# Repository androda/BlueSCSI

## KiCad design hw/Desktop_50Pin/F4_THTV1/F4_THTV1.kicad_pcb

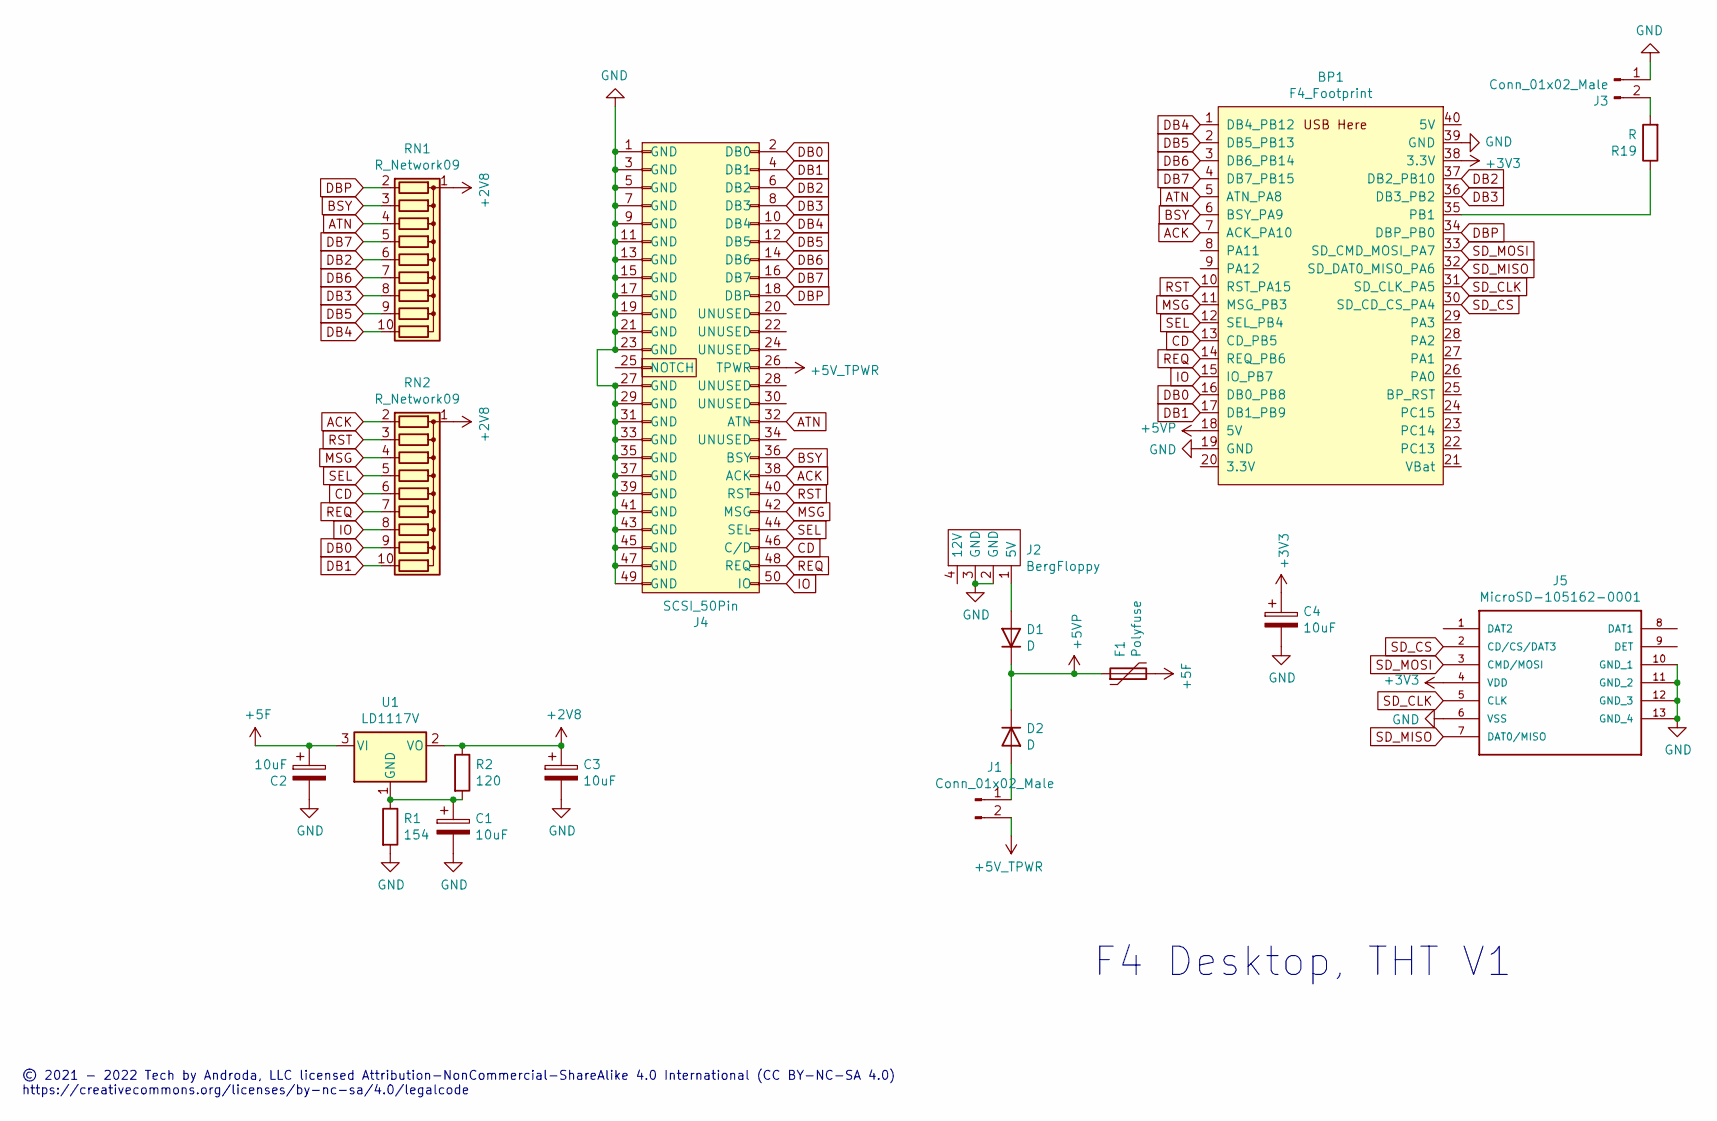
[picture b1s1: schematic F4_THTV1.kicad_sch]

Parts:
BP1: F4_Footprint; BluePillModule
C1, C2, C3, C4: 10uF; C_1210_3225Metric_Pad1.42x2.65mm_HandSolder
D1, D2: D; D_A-405_P7.62mm_Horizontal
F1: Polyfuse; Fuse_BelFuse_0ZRE0005FF_L8.3mm_W3.8mm
J1, J3: Conn_01x02_Male; PinHeader_1x02_P2.54mm_Vertical
J2: BergFloppy; BergFloppy_RightAngle
J4: SCSI_50Pin; SCSI_Internal_50Pin
J5: MicroSD-105162-0001; microsd_molex_1051620001; MANUFACTURER_PART_NUMBER 105162-0001; MOUSER_PART_NUMBER 538-105162-0001
R1: 154; R_Axial_DIN0207_L6.3mm_D2.5mm_P10.16mm_Horizontal
R2: 120; R_Axial_DIN0204_L3.6mm_D1.6mm_P5.08mm_Vertical
R19: R; R_Axial_DIN0207_L6.3mm_D2.5mm_P7.62mm_Horizontal
RN1, RN2: R_Network09; R_Array_SIP10
U1: LD1117V; TO-220-3_Horizontal_TabDown

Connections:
+2V8: C3.1, R2.1, RN1.1 (common), RN2.1 (common), U1.2 (VO)
+3V3: BP1.38 (3.3V), C4.1, J5.4 (VDD)
+5F: C2.1, F1.2, U1.3 (VI)
+5V: J1.2, J4.26 (TPWR)
+5VP: BP1.18 (5V), D1.1 (K), D2.1 (K), F1.1
ACK: BP1.7 (ACK_PA10), J4.38 (ACK), RN2.2 (R1)
ATN: BP1.5 (ATN_PA8), J4.32 (ATN), RN1.4 (R3)
BSY: BP1.6 (BSY_PA9), J4.36 (BSY), RN1.3 (R2)
CD: BP1.13 (CD_PB5), J4.46 (C/D), RN2.6 (R5)
DB0: BP1.16 (DB0_PB8), J4.2 (DB0), RN2.9 (R8)
DB1: BP1.17 (DB1_PB9), J4.4 (DB1), RN2.10 (R9)
DB2: BP1.37 (DB2_PB10), J4.6 (DB2), RN1.6 (R5)
DB3: BP1.36 (DB3_PB2), J4.8 (DB3), RN1.8 (R7)
DB4: BP1.1 (DB4_PB12), J4.10 (DB4), RN1.10 (R9)
DB5: BP1.2 (DB5_PB13), J4.12 (DB5), RN1.9 (R8)
DB6: BP1.3 (DB6_PB14), J4.14 (DB6), RN1.7 (R6)
DB7: BP1.4 (DB7_PB15), J4.16 (DB7), RN1.5 (R4)
DBP: BP1.34 (DBP_PB0), J4.18 (DBP), RN1.2 (R1)
GND: BP1.19 (GND), BP1.39 (GND), C1.2, C2.2, C3.2, C4.2, J2.2 (GND), J2.3 (GND), J3.1, J4.1 (GND), J4.3 (GND), J4.5 (GND), J4.7 (GND), J4.9 (GND), J4.11 (GND), J4.13 (GND), J4.15 (GND), J4.17 (GND), J4.19 (GND), J4.21 (GND), J4.23 (GND), J4.27 (GND), J4.29 (GND), J4.31 (GND), J4.33 (GND), J4.35 (GND), J4.37 (GND), J4.39 (GND), J4.41 (GND), J4.43 (GND), J4.45 (GND), J4.47 (GND), J4.49 (GND), J5.6 (VSS), J5.10 (GND_1), J5.11 (GND_2), J5.12 (GND_3), J5.13 (GND_4), R1.2
IO: BP1.15 (IO_PB7), J4.50 (IO), RN2.8 (R7)
MSG: BP1.11 (MSG_PB3), J4.42 (MSG), RN2.4 (R3)
unnamed: BP1.35 (PB1), R19.1
unnamed: C1.1, R1.1, R2.2, U1.1 (GND)
unnamed: D1.2 (A), J2.1 (5V)
unnamed: D2.2 (A), J1.1
unnamed: J3.2, R19.2
REQ: BP1.14 (REQ_PB6), J4.48 (REQ), RN2.7 (R6)
RST: BP1.10 (RST_PA15), J4.40 (RST), RN2.3 (R2)
SD_CLK: BP1.31 (SD_CLK_PA5), J5.5 (CLK)
SD_CS: BP1.30 (SD_CD_CS_PA4), J5.2 (CD/CS/DAT3)
SD_MISO: BP1.32 (SD_DAT0_MISO_PA6), J5.7 (DAT0/MISO)
SD_MOSI: BP1.33 (SD_CMD_MOSI_PA7), J5.3 (CMD/MOSI)
SEL: BP1.12 (SEL_PB4), J4.44 (SEL), RN2.5 (R4)

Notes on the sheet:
F4 Desktop, THT V1
© 2021 - 2022 Tech by Androda, LLC licensed Attribution-NonCommercial-ShareAlike 4.0 International (CC BY-NC-SA 4.0) https://creativecommons.org/licenses/by-nc-sa/4.0/legalcode

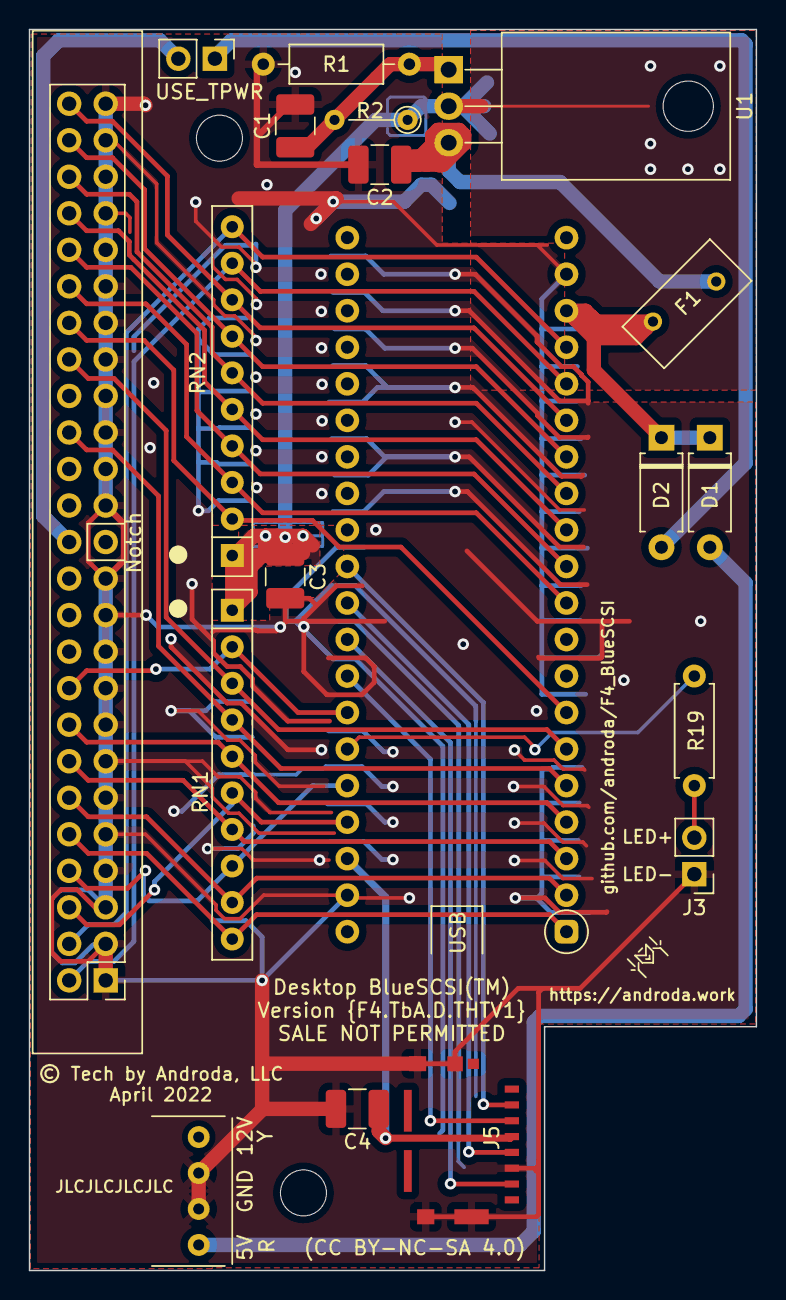
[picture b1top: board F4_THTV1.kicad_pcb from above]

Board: 2 copper layers, 50.5 x 86.3 mm, 19 parts (0 on the bottom side), 33 nets.

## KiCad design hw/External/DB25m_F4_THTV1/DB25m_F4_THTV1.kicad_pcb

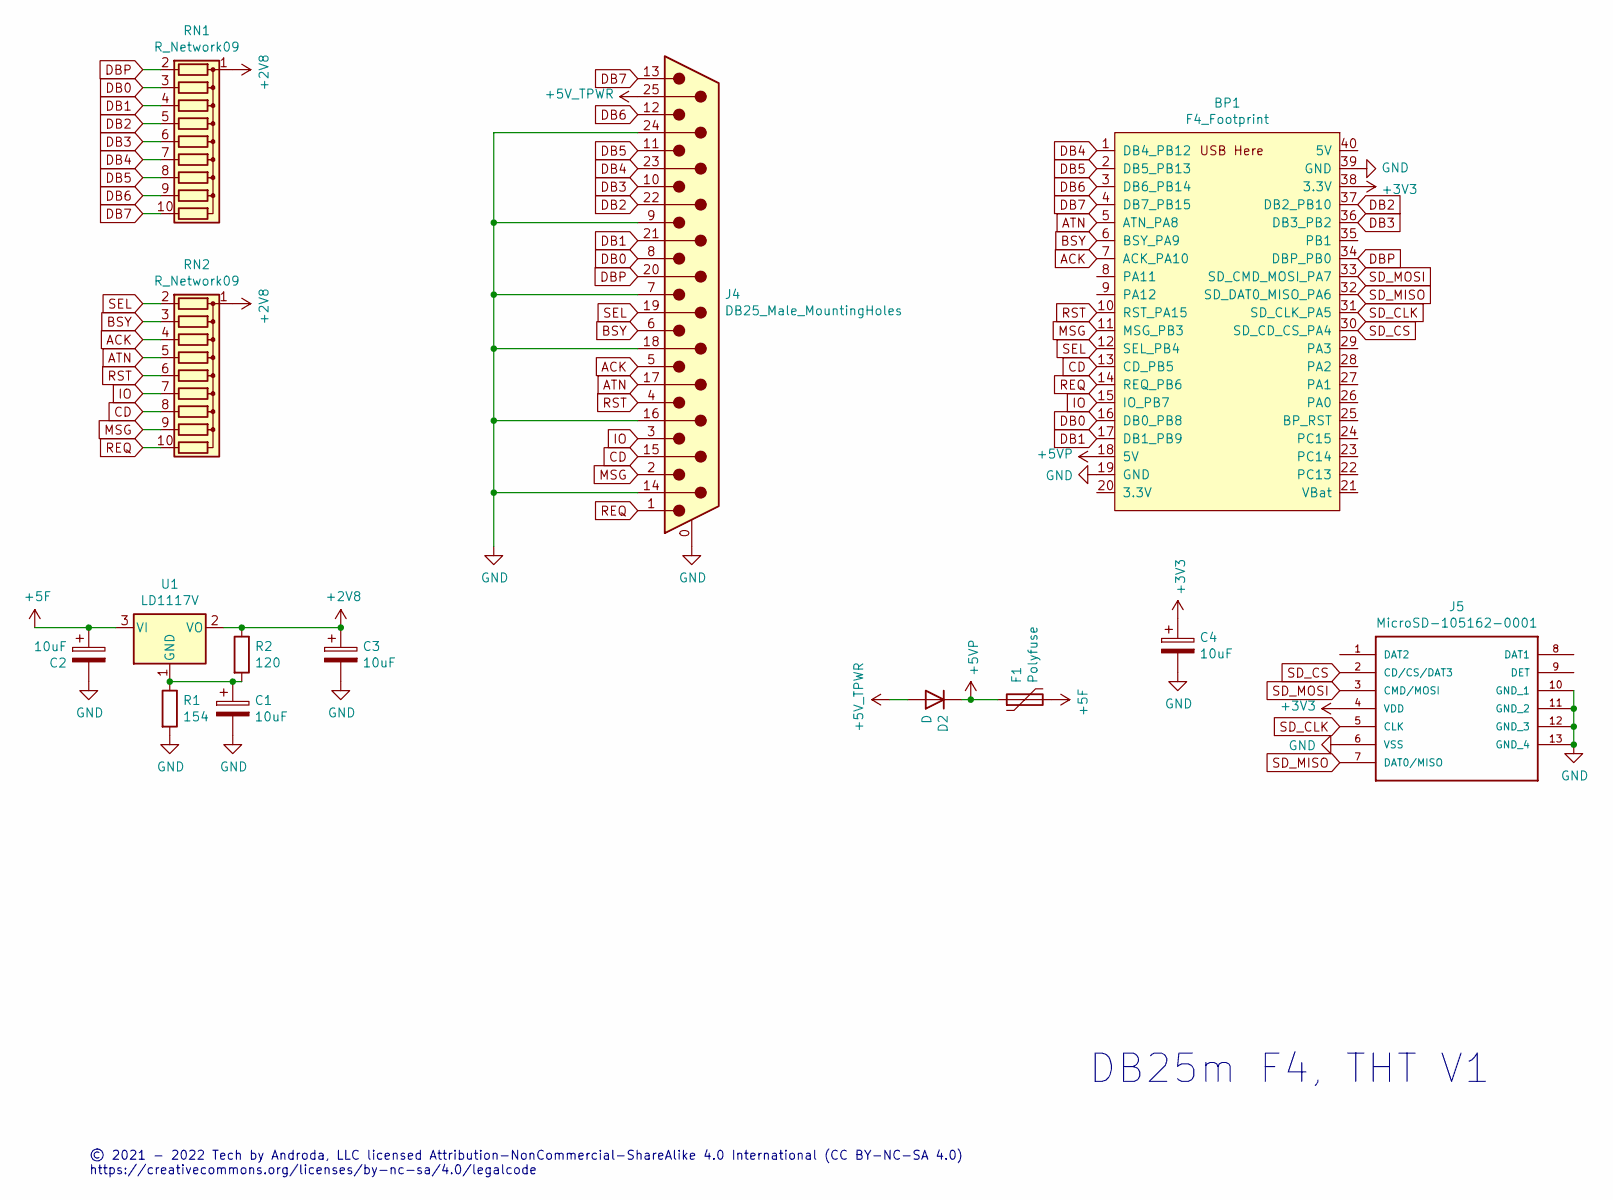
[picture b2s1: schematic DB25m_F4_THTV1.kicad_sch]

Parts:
BP1: F4_Footprint; BluePillModule
C1, C2, C3, C4: 10uF; C_1210_3225Metric_Pad1.42x2.65mm_HandSolder
D2: D; D_A-405_P10.16mm_Horizontal
F1: Polyfuse; Fuse_BelFuse_0ZRE0005FF_L8.3mm_W3.8mm
J4: DB25_Male_MountingHoles; DSUB-25_Male_Horizontal_P2.77x2.84mm_EdgePinOffset7.70mm_Ho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
J5: MicroSD-105162-0001; microsd_molex_1051620001; MANUFACTURER_PART_NUMBER 105162-0001; MOUSER_PART_NUMBER 538-105162-0001
R1: 154; R_Axial_DIN0207_L6.3mm_D2.5mm_P10.16mm_Horizontal
R2: 120; R_Axial_DIN0204_L3.6mm_D1.6mm_P5.08mm_Vertical
RN1, RN2: R_Network09; R_Array_SIP10
U1: LD1117V; TO-220-3_Horizontal_TabDown

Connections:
+2V8: C3.1, R2.1, RN1.1 (common), RN2.1 (common), U1.2 (VO)
+3V3: BP1.38 (3.3V), C4.1, J5.4 (VDD)
+5F: C2.1, F1.2, U1.3 (VI)
+5V: D2.2 (A), J4.25
+5VP: BP1.18 (5V), D2.1 (K), F1.1
ACK: BP1.7 (ACK_PA10), J4.5, RN2.4 (R3)
ATN: BP1.5 (ATN_PA8), J4.17, RN2.5 (R4)
BSY: BP1.6 (BSY_PA9), J4.6, RN2.3 (R2)
CD: BP1.13 (CD_PB5), J4.15, RN2.8 (R7)
DB0: BP1.16 (DB0_PB8), J4.8, RN1.3 (R2)
DB1: BP1.17 (DB1_PB9), J4.21, RN1.4 (R3)
DB2: BP1.37 (DB2_PB10), J4.22, RN1.5 (R4)
DB3: BP1.36 (DB3_PB2), J4.10, RN1.6 (R5)
DB4: BP1.1 (DB4_PB12), J4.23, RN1.7 (R6)
DB5: BP1.2 (DB5_PB13), J4.11, RN1.8 (R7)
DB6: BP1.3 (DB6_PB14), J4.12, RN1.9 (R8)
DB7: BP1.4 (DB7_PB15), J4.13, RN1.10 (R9)
DBP: BP1.34 (DBP_PB0), J4.20, RN1.2 (R1)
GND: BP1.19 (GND), BP1.39 (GND), C1.2, C2.2, C3.2, C4.2, J4.0 (PAD), J4.7, J4.9, J4.14, J4.16, J4.18, J4.24, J5.6 (VSS), J5.10 (GND_1), J5.11 (GND_2), J5.12 (GND_3), J5.13 (GND_4), R1.2
IO: BP1.15 (IO_PB7), J4.3, RN2.7 (R6)
MSG: BP1.11 (MSG_PB3), J4.2, RN2.9 (R8)
unnamed: C1.1, R1.1, R2.2, U1.1 (GND)
REQ: BP1.14 (REQ_PB6), J4.1, RN2.10 (R9)
RST: BP1.10 (RST_PA15), J4.4, RN2.6 (R5)
SD_CLK: BP1.31 (SD_CLK_PA5), J5.5 (CLK)
SD_CS: BP1.30 (SD_CD_CS_PA4), J5.2 (CD/CS/DAT3)
SD_MISO: BP1.32 (SD_DAT0_MISO_PA6), J5.7 (DAT0/MISO)
SD_MOSI: BP1.33 (SD_CMD_MOSI_PA7), J5.3 (CMD/MOSI)
SEL: BP1.12 (SEL_PB4), J4.19, RN2.2 (R1)

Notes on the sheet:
© 2021 - 2022 Tech by Androda, LLC licensed Attribution-NonCommercial-ShareAlike 4.0 International (CC BY-NC-SA 4.0) https://creativecommons.org/licenses/by-nc-sa/4.0/legalcode
DB25m F4, THT V1

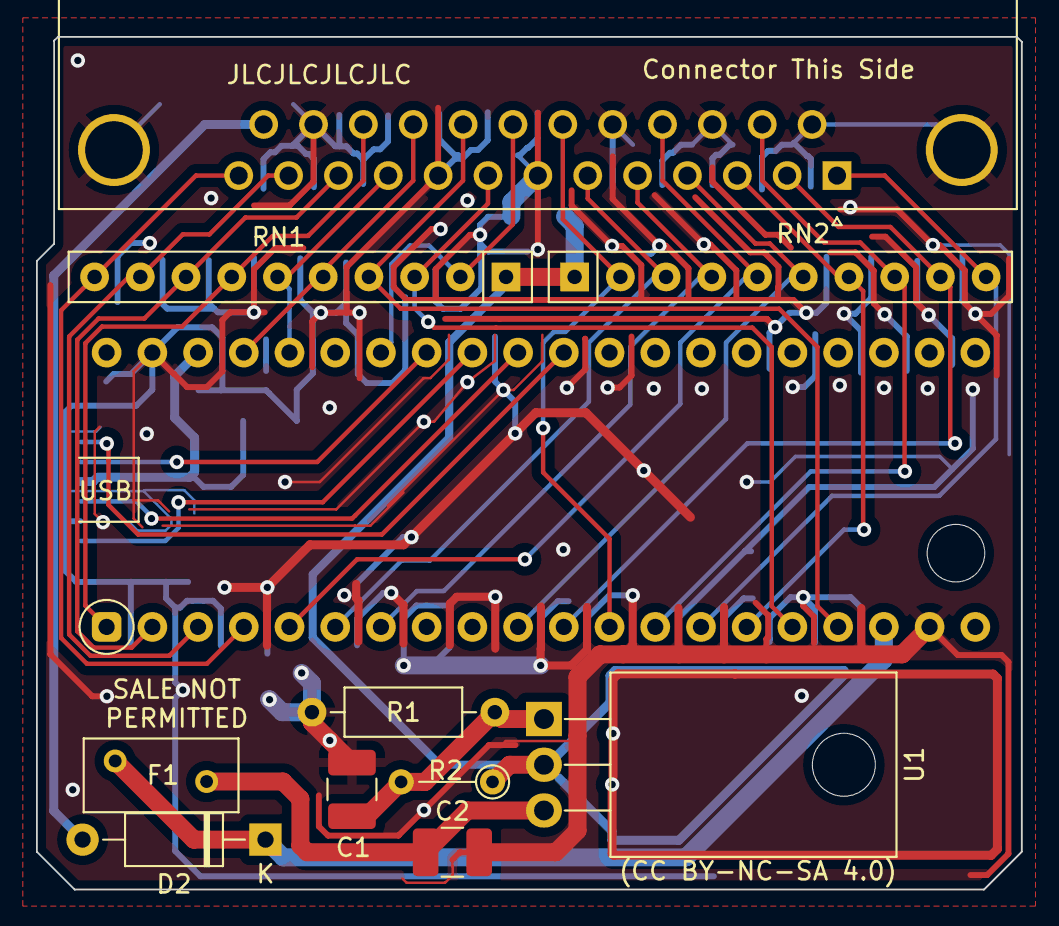
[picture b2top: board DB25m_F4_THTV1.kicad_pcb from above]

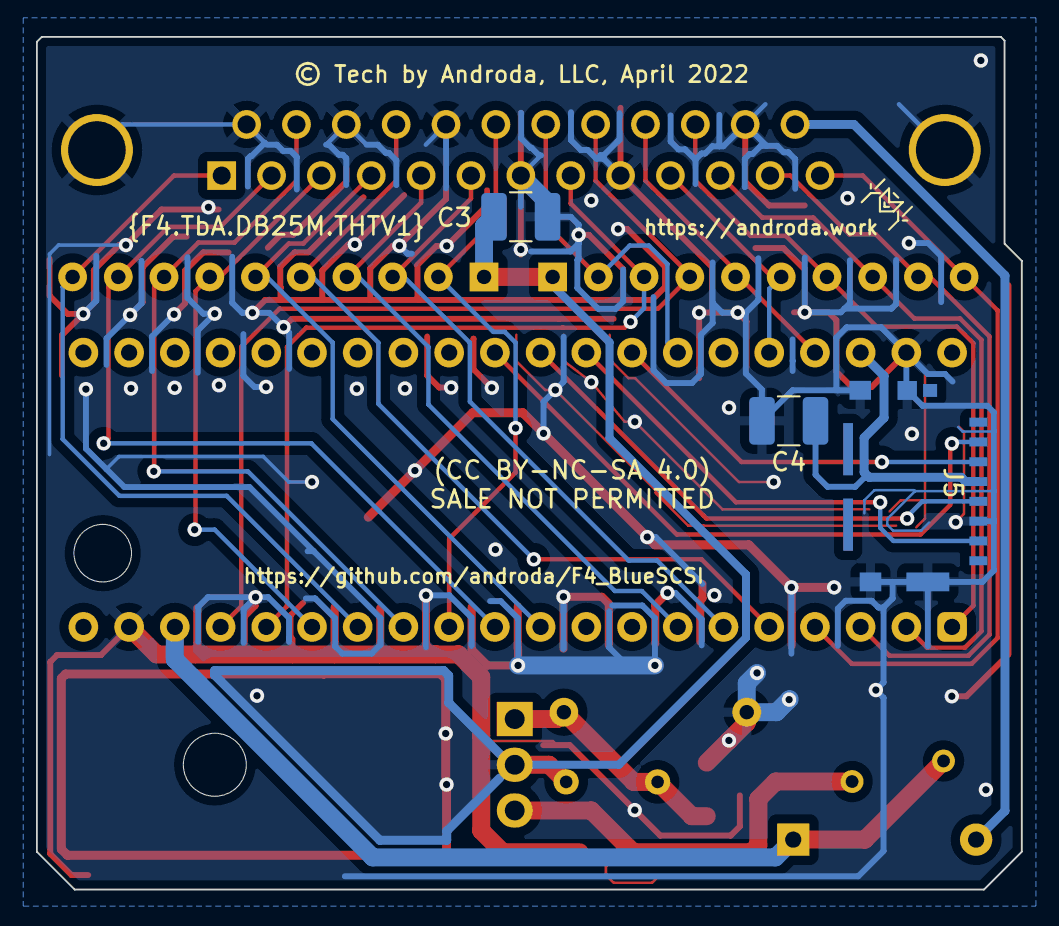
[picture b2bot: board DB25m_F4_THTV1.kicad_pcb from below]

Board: 2 copper layers, 54.7 x 47.4 mm, 14 parts (3 on the bottom side), 29 nets.

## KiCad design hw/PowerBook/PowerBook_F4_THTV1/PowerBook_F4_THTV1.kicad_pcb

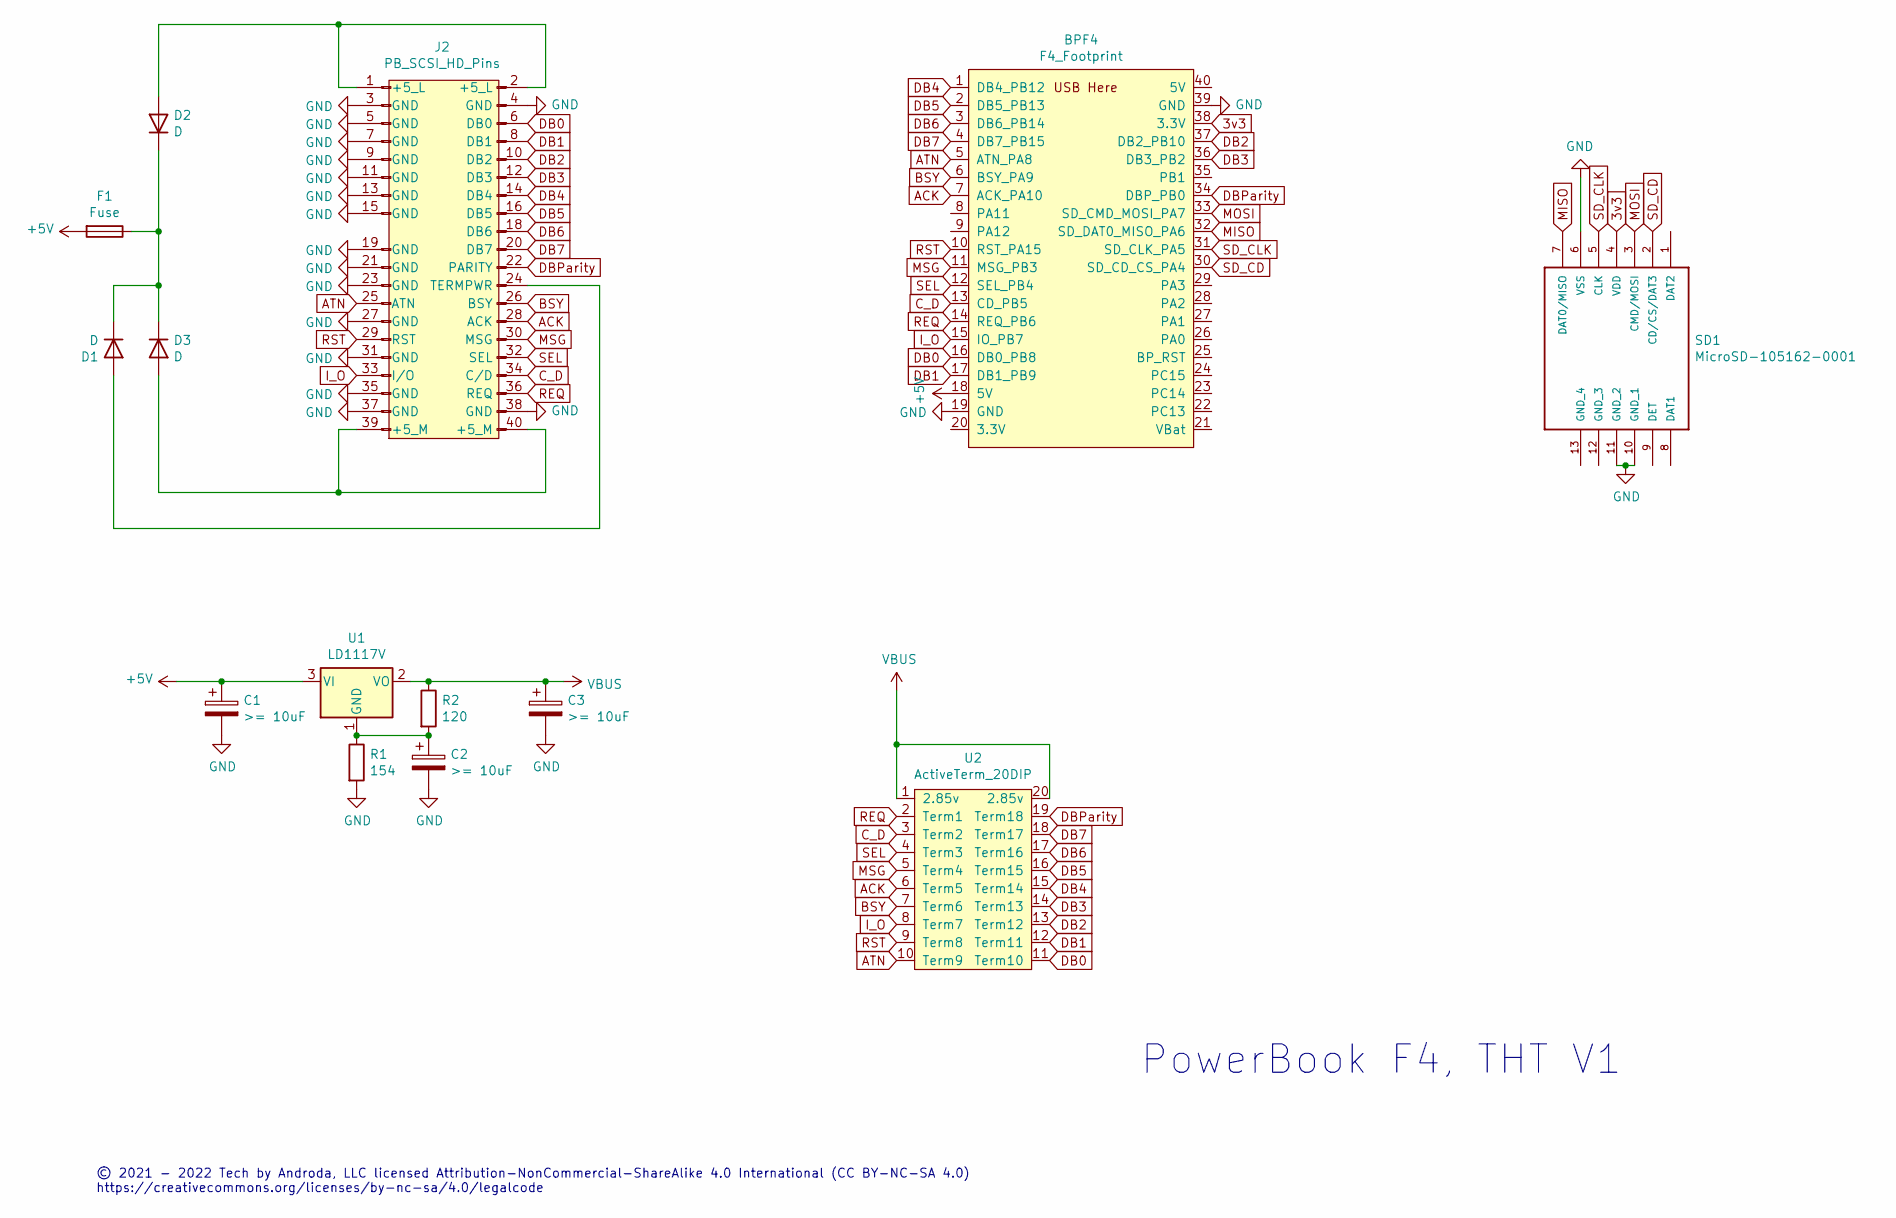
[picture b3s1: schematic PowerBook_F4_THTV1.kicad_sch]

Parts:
BPF4: F4_Footprint; BluePillModule
C1, C2, C3: >= 10uF; C_1206_3216Metric_Pad1.42x1.75mm_HandSolder
D1, D2, D3: D; D_A-405_P10.16mm_Horizontal
F1: Fuse; Fuse_BelFuse_0ZRE0005FF_L8.3mm_W3.8mm
J2: PB_SCSI_HD_Pins; PowerBook_SCSI_40Pin_UpsideDown
R1: 154; R_Axial_DIN0204_L3.6mm_D1.6mm_P7.62mm_Horizontal
R2: 120; R_Axial_DIN0204_L3.6mm_D1.6mm_P5.08mm_Vertical
SD1: MicroSD-105162-0001; microsd_molex_1051620001; MANUFACTURER_PART_NUMBER 105162-0001; MOUSER_PART_NUMBER 538-105162-0001
U1: LD1117V; TO-220-3_Horizontal_TabDown
U2: ActiveTerm_20DIP; DIP-20_W7.62mm_Socket

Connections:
3v3: BPF4.38 (3.3V), SD1.4 (VDD)
+5V: BPF4.18 (5V), C1.1, F1.2, U1.3 (VI)
ACK: BPF4.7 (ACK_PA10), J2.28 (ACK), U2.6 (Term5)
ATN: BPF4.5 (ATN_PA8), J2.25 (ATN), U2.10 (Term9)
BSY: BPF4.6 (BSY_PA9), J2.26 (BSY), U2.7 (Term6)
C_D: BPF4.13 (CD_PB5), J2.34 (C/D), U2.3 (Term2)
DB0: BPF4.16 (DB0_PB8), J2.6 (DB0), U2.11 (Term10)
DB1: BPF4.17 (DB1_PB9), J2.8 (DB1), U2.12 (Term11)
DB2: BPF4.37 (DB2_PB10), J2.10 (DB2), U2.13 (Term12)
DB3: BPF4.36 (DB3_PB2), J2.12 (DB3), U2.14 (Term13)
DB4: BPF4.1 (DB4_PB12), J2.14 (DB4), U2.15 (Term14)
DB5: BPF4.2 (DB5_PB13), J2.16 (DB5), U2.16 (Term15)
DB6: BPF4.3 (DB6_PB14), J2.18 (DB6), U2.17 (Term16)
DB7: BPF4.4 (DB7_PB15), J2.20 (DB7), U2.18 (Term17)
DBParity: BPF4.34 (DBP_PB0), J2.22 (PARITY), U2.19 (Term18)
GND: BPF4.19 (GND), BPF4.39 (GND), C1.2, C2.2, C3.2, J2.3 (GND), J2.4 (GND), J2.5 (GND), J2.7 (GND), J2.9 (GND), J2.11 (GND), J2.13 (GND), J2.15 (GND), J2.19 (GND), J2.21 (GND), J2.23 (GND), J2.27 (GND), J2.31 (GND), J2.35 (GND), J2.37 (GND), J2.38 (GND), R1.2, SD1.6 (VSS), SD1.10 (GND_1), SD1.11 (GND_2)
I_O: BPF4.15 (IO_PB7), J2.33 (I/O), U2.8 (Term7)
MISO: BPF4.32 (SD_DAT0_MISO_PA6), SD1.7 (DAT0/MISO)
MOSI: BPF4.33 (SD_CMD_MOSI_PA7), SD1.3 (CMD/MOSI)
MSG: BPF4.11 (MSG_PB3), J2.30 (MSG), U2.5 (Term4)
unnamed: C2.1, R1.1, R2.2, U1.1 (GND)
unnamed: D1.1 (K), D2.1 (K), D3.1 (K), F1.1
unnamed: D1.2 (A), J2.24 (TERMPWR)
unnamed: D2.2 (A), J2.1 (+5_L), J2.2 (+5_L)
unnamed: D3.2 (A), J2.39 (+5_M), J2.40 (+5_M)
REQ: BPF4.14 (REQ_PB6), J2.36 (REQ), U2.2 (Term1)
RST: BPF4.10 (RST_PA15), J2.29 (RST), U2.9 (Term8)
SD_CD: BPF4.30 (SD_CD_CS_PA4), SD1.2 (CD/CS/DAT3)
SD_CLK: BPF4.31 (SD_CLK_PA5), SD1.5 (CLK)
SEL: BPF4.12 (SEL_PB4), J2.32 (SEL), U2.4 (Term3)
VBUS: C3.1, R2.1, U1.2 (VO), U2.1 (2.85v), U2.20 (2.85v)

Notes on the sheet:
PowerBook F4, THT V1
© 2021 - 2022 Tech by Androda, LLC licensed Attribution-NonCommercial-ShareAlike 4.0 International (CC BY-NC-SA 4.0) https://creativecommons.org/licenses/by-nc-sa/4.0/legalcode

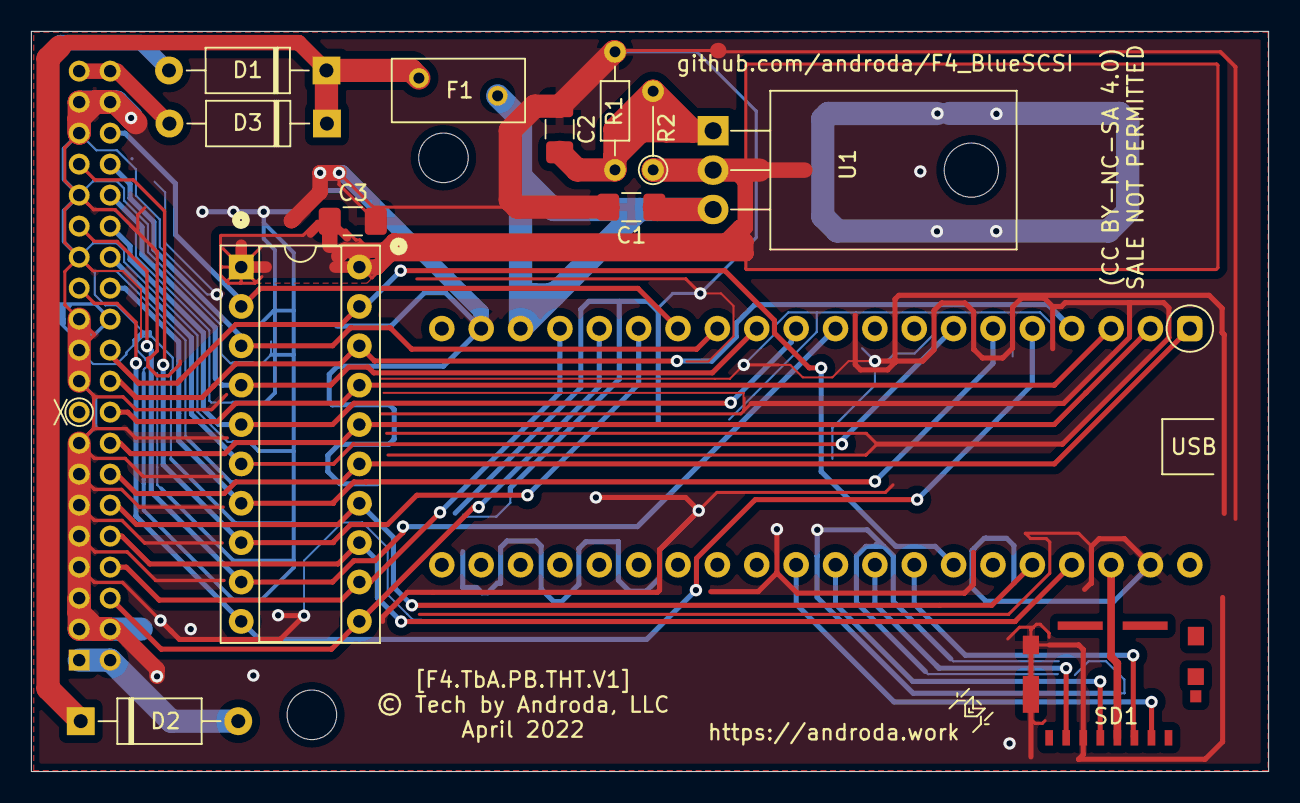
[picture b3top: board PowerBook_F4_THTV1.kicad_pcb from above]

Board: 2 copper layers, 79.8 x 47.8 mm, 14 parts (0 on the bottom side), 31 nets.

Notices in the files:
hw/Desktop_50Pin/F4_THTV1/F4_THTV1.kicad_pcb:
© Tech by Androda, LLC
hw/External/DB25m_F4_THTV1/DB25m_F4_THTV1.kicad_pcb:
© Tech by Androda, LLC, April 2022
